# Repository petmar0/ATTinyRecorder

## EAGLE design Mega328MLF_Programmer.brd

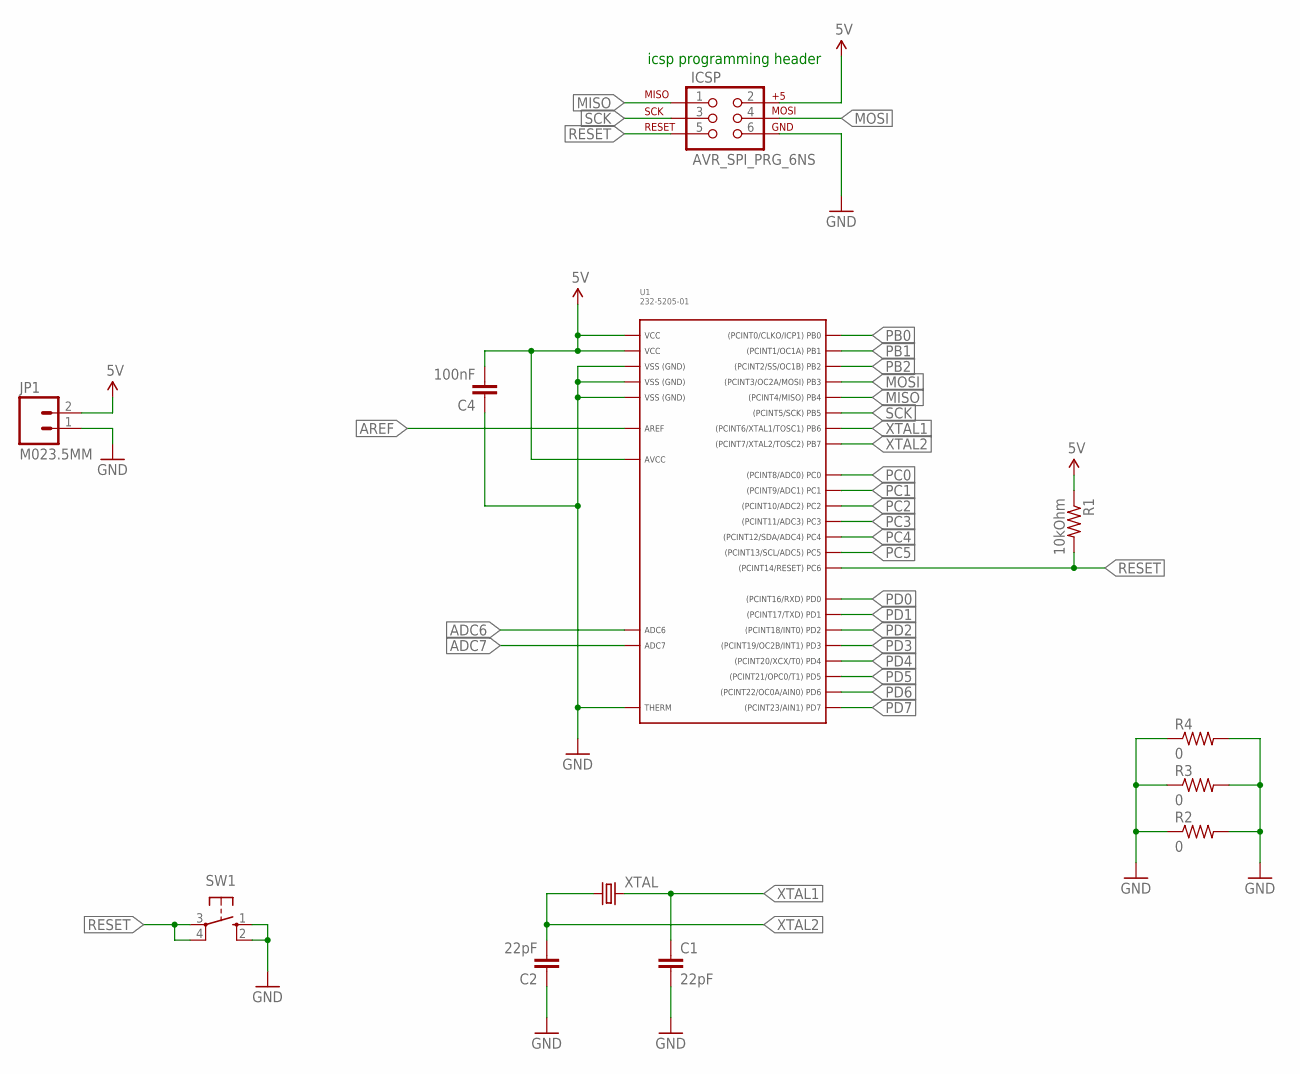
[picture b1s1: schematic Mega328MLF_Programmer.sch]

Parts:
C1, C2: 22pF; CAP-PTH-SMALL2
C4: 100nF; CAP-PTH-SMALL2
ICSP: AVR_SPI_PRG_6NS; 2X3-NS
JP1: M023.5MM; SCREWTERMINAL-3.5MM-2
R1: 10kOhm; 0204/7
R2, R3, R4: 0; 0204/7
SW1: 10-XX; B3F-10XX
U1: 232-5205-01
XTAL: CRYSTALHC49UV; HC49U-V

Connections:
5V: C4.2, ICSP.2, JP1.2, R1.1, U1.4 (VCC), U1.6 (VCC), U1.18 (AVCC)
ADC6: U1.19 (ADC6)
ADC7: U1.22 (ADC7)
AREF: U1.20 (AREF)
GND: C1.2, C2.1, C4.1, ICSP.6, JP1.1, R2.1, R2.2, R3.1, R3.2, R4.1, R4.2, SW1.1 (S), SW1.2 (S1), U1.3 (GND), U1.5 (GND), U1.21 (GND), U1.THERM
MISO: ICSP.1, U1.16 (PB4)
MOSI: ICSP.4, U1.15 (PB3)
PB0: U1.12 (PB0)
PB1: U1.13 (PB1)
PB2: U1.14 (PB2)
PC0: U1.23 (PC0)
PC1: U1.24 (PC1)
PC2: U1.25 (PC2)
PC3: U1.26 (PC3)
PC4: U1.27 (PC4)
PC5: U1.28 (PC5)
PD0: U1.30 (PD0)
PD1: U1.31 (PD1)
PD2: U1.32 (PD2)
PD3: U1.1 (PD3)
PD4: U1.2 (PD4)
PD5: U1.9 (PD5)
PD6: U1.10 (PD6)
PD7: U1.11 (PD7)
RESET: ICSP.5, R1.2, SW1.3, SW1.4 (P1), U1.29 (PC6)
SCK: ICSP.3, U1.17 (PB5)
XTAL1: C1.1, U1.7 (PB6), XTAL.2
XTAL2: C2.2, U1.8 (PB7), XTAL.1

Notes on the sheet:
icsp programming header

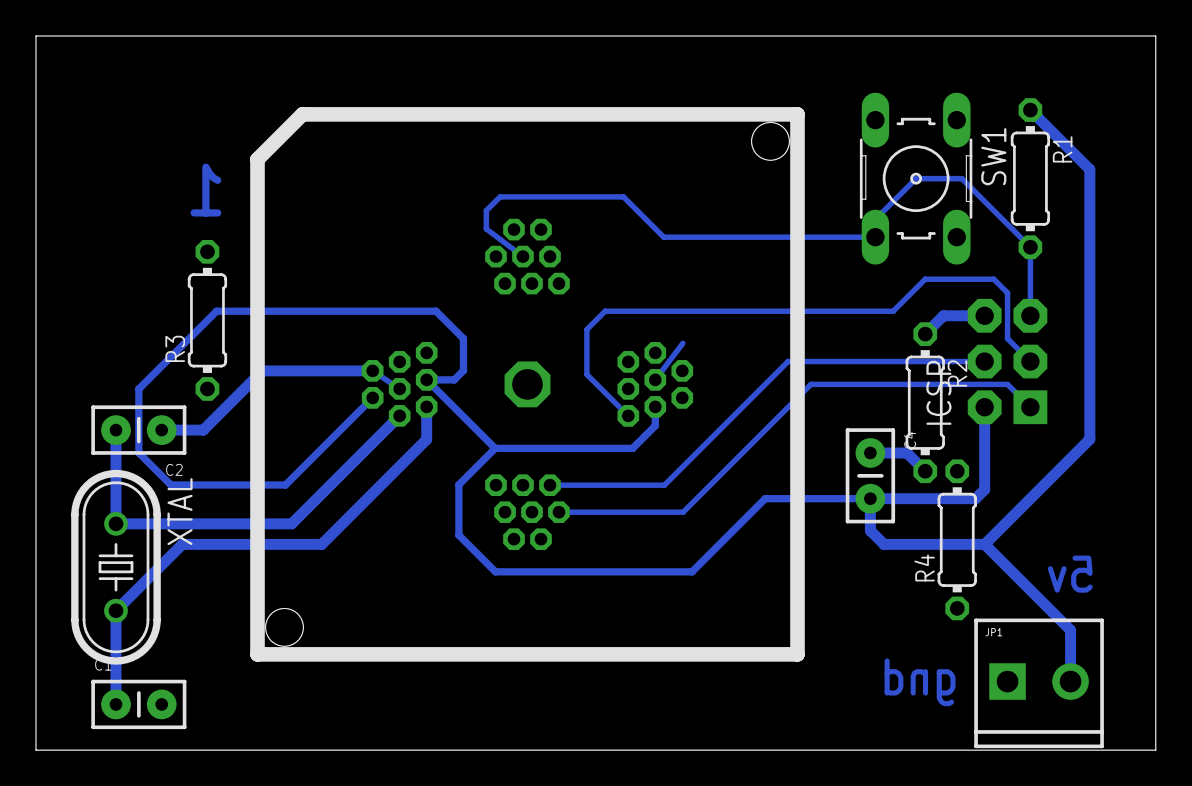
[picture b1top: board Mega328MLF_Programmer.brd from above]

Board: 2 copper layers, 62.2 x 39.7 mm, 12 parts (0 on the bottom side), 8 nets.

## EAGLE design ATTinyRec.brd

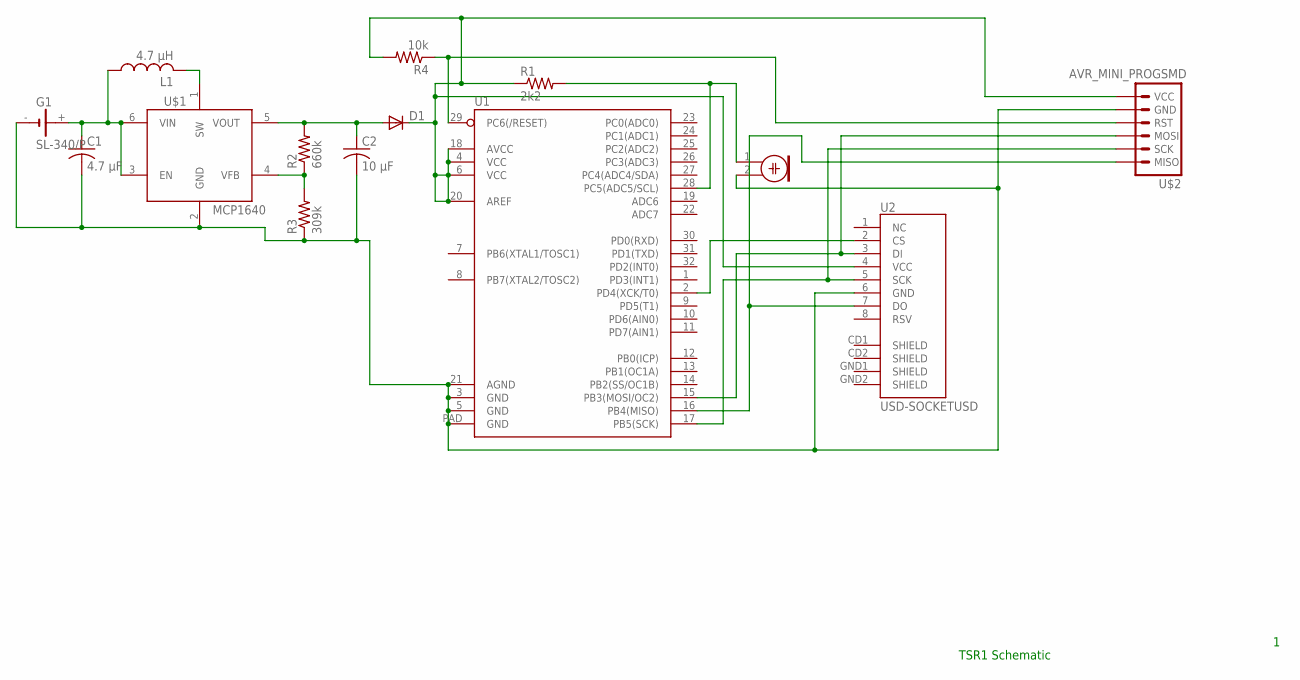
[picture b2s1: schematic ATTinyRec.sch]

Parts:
C1: 4.7 µF; C0402
C2: 10 µF; C0402
D1: DIODE-DO214AC; DO214AC
G1: SL-340/P; BEL/P
L1: 4.7 µH; L2012C
M1: ELECTRET_MICROPHON-WM-62PC/62PK; WM-62PC/62PK
R1: 2k2; R0402
R2: 660k; R0402
R3: 309k; R0402
R4: 10k; R0402
U1: ATMEGA328P_MLFMLF32; MLF32-PAD
U2: USD-SOCKETUSD; USD-SOCKET-PP
U$1: MCP1640; SOT23-6
U$2: AVR_MINI_PROGSMD; AVR_MINI_PROG

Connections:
GND: C1.2, C2.2, G1.-, M1.2, R3.1, U1.3 (GND), U1.5 (GND), U1.21 (AGND), U1.PAD (GND), U2.6 (GND), U$1.2 (GND), U$2.2 (GND)
MISO: U1.16 (PB4(MISO)), U2.7 (DO), U$2.6 (MISO)
MOSI: U1.15 (PB3(MOSI/OC2)), U2.3 (DI), U$2.4 (MOSI)
unnamed: C1.1, G1.+, L1.1, U$1.3 (EN), U$1.6 (VIN)
unnamed: R2.1, R3.2, U$1.4 (VFB)
unnamed: L1.2, U$1.1 (SW)
unnamed: M1.1, R1.2, U1.28 (PC5(ADC5/SCL))
unnamed: C2.1, D1.A, R2.2, U$1.5 (VOUT)
unnamed: U1.2 (PD4(XCK/T0)), U2.2 (CS)
RESET: R4.1, U1.29 (PC6(/RESET)), U$2.3 (RST)
SCK: U1.17 (PB5(SCK)), U2.5 (SCK), U$2.5 (SCK)
VCC: D1.C, R1.1, R4.2, U1.4 (VCC), U1.6 (VCC), U1.18 (AVCC), U1.20 (AREF), U2.4 (VCC), U$2.1 (VCC)

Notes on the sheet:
TSR1 Schematic

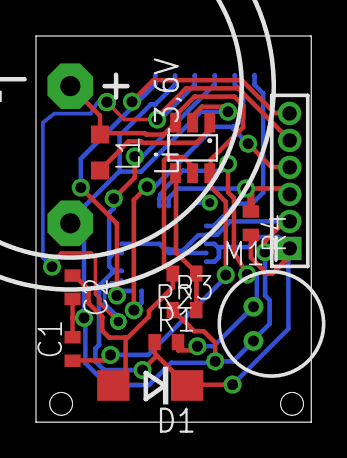
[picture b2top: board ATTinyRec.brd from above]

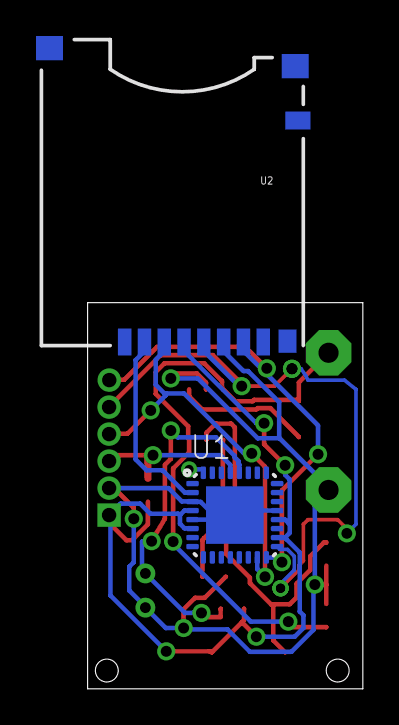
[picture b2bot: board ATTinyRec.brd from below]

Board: 2 copper layers, 15.3 x 21.5 mm, 14 parts (2 on the bottom side), 12 nets.

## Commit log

2015-05-06 Reorg
2015-05-06 Routing and added LED
2015-05-06 Debugging
2015-05-07 Component Replacements
2015-05-13 Routed
2015-05-13 Routing
2015-05-18 Latest Updates
2015-05-19 Gerber and board ordering zip done
2015-05-20 Board PDF
2015-05-20 Board PDFs
2015-06-01 removing temporary / artifact files
2015-06-01 refactoring gerbers into a subdirectory and removing superfluous outdated pdfs
2015-06-01 removing project file
2015-06-01 remade board and schematic consistent
2015-06-01 added pullup resistor
2015-06-01 Added Schematic PDF
2015-06-01 Fixed Board Layout
2015-06-01 Updated BoM
2015-06-02 Updated Code and Board
2015-06-04 added board design for MLF programming off circuit
2015-06-12 Added Hex File
2015-06-12 Adding Board PDFs

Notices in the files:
parts and their libraries:
SparkFun-Connectors: Licensing: CC v3.0 Share-Alike You are welcome to use this library for commercial purposes.
GeekAmmo: Licensing:Creative Commons ShareAlike 4.0 International - https://creativecommons.org/licenses/by-sa/4.0
